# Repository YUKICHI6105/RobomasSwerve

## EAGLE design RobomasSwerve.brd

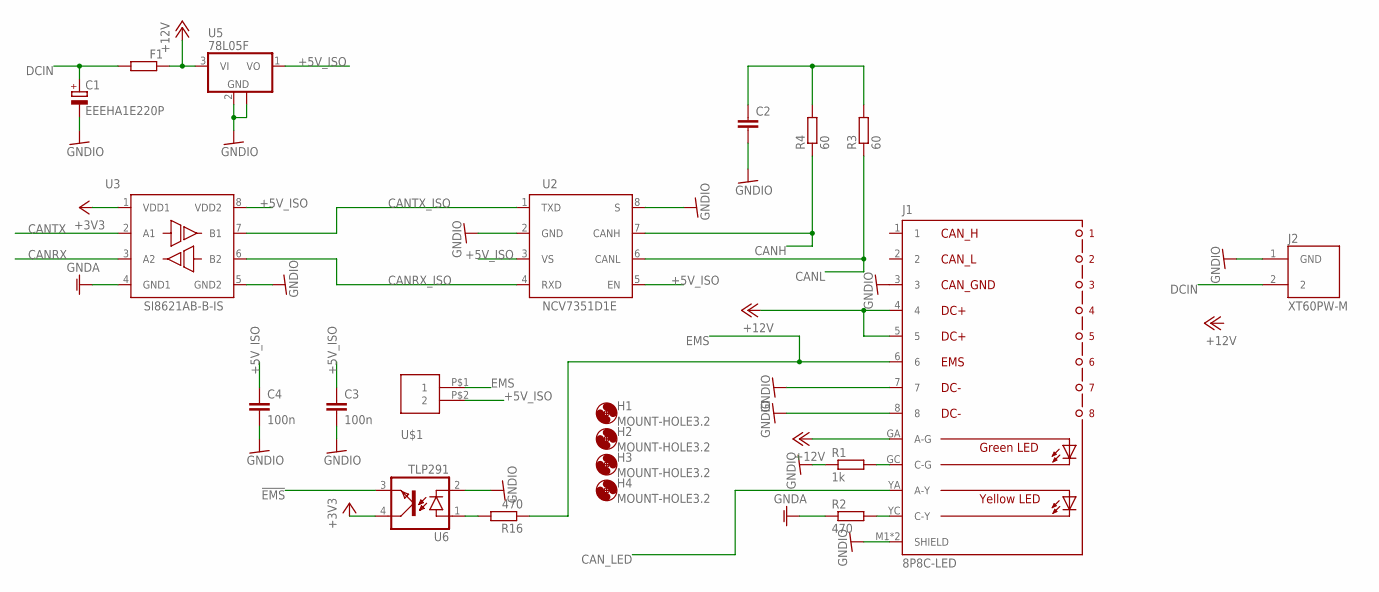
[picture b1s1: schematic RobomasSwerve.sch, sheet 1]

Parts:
C1: EEEHA1E220P; 153CLV-0605
C2: C-EUC0603; C0603
C3, C4: 100n; C0603
F1: R-EU_R1206; R1206
H1, H2, H3, H4: MOUNT-HOLE3.2; 3,2
J1: 8P8C-LED
J2: XT60PW-M; AMASS_XT60PW-M
R1: 1k; R0603
R2, R16: 470; R0603
R3, R4: 60; R0603
U2: NCV7351D1E; SO08
U3: SI8621AB-B-IS; SO08
U5: 78L05F; SOT89
U6: TLP291; MINI-FLAT-4
U$1: XH-2-STRAIGHT; CON-XH-2-STRAIGHT

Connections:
!EMS: U6.3 (EMIT); also elsewhere on the board
+3V3: U3.1 (VDD1), U6.4 (COL); also elsewhere on the board
+5V_ISO: C3.1, C4.1, U2.3 (VS), U2.5 (EN), U3.8 (VDD2), U5.1 (VO), U$1.P$2 (2)
+12V: F1.1, J1.4, J1.5, J1.GA (A-G), U5.3 (VI)
CANH: R4.1, U2.7 (CANH)
CANL: R3.1, U2.6 (CANL)
CANRX: U3.3 (A2); also elsewhere on the board
CANRX_ISO: U2.4 (RXD), U3.6 (B2)
CANTX: U3.2 (A1); also elsewhere on the board
CANTX_ISO: U2.1 (TXD), U3.7 (B1)
CAN_LED: J1.YA (A-Y); also elsewhere on the board
DCIN: C1.+, F1.2, J2.2
EMS: J1.6, R16.1, U$1.P$1 (1)
GNDA: R2.1, U3.4 (GND1); also elsewhere on the board
GNDIO: C1.-, C2.2, C3.2, C4.2, J1.3, J1.7, J1.8, J1.M1 (SHIELD), J1.M2 (SHIELD), J2.1 (GND), R1.1, U2.2 (GND), U2.8 (S), U3.5 (GND2), U5.2 (GND), U5.2@1 (GND), U6.2 (C)
unnamed: J1.GC (C-G), R1.2
unnamed: J1.YC (C-Y), R2.2
unnamed: C2.1, R3.2, R4.2
unnamed: R16.2, U6.1 (A)

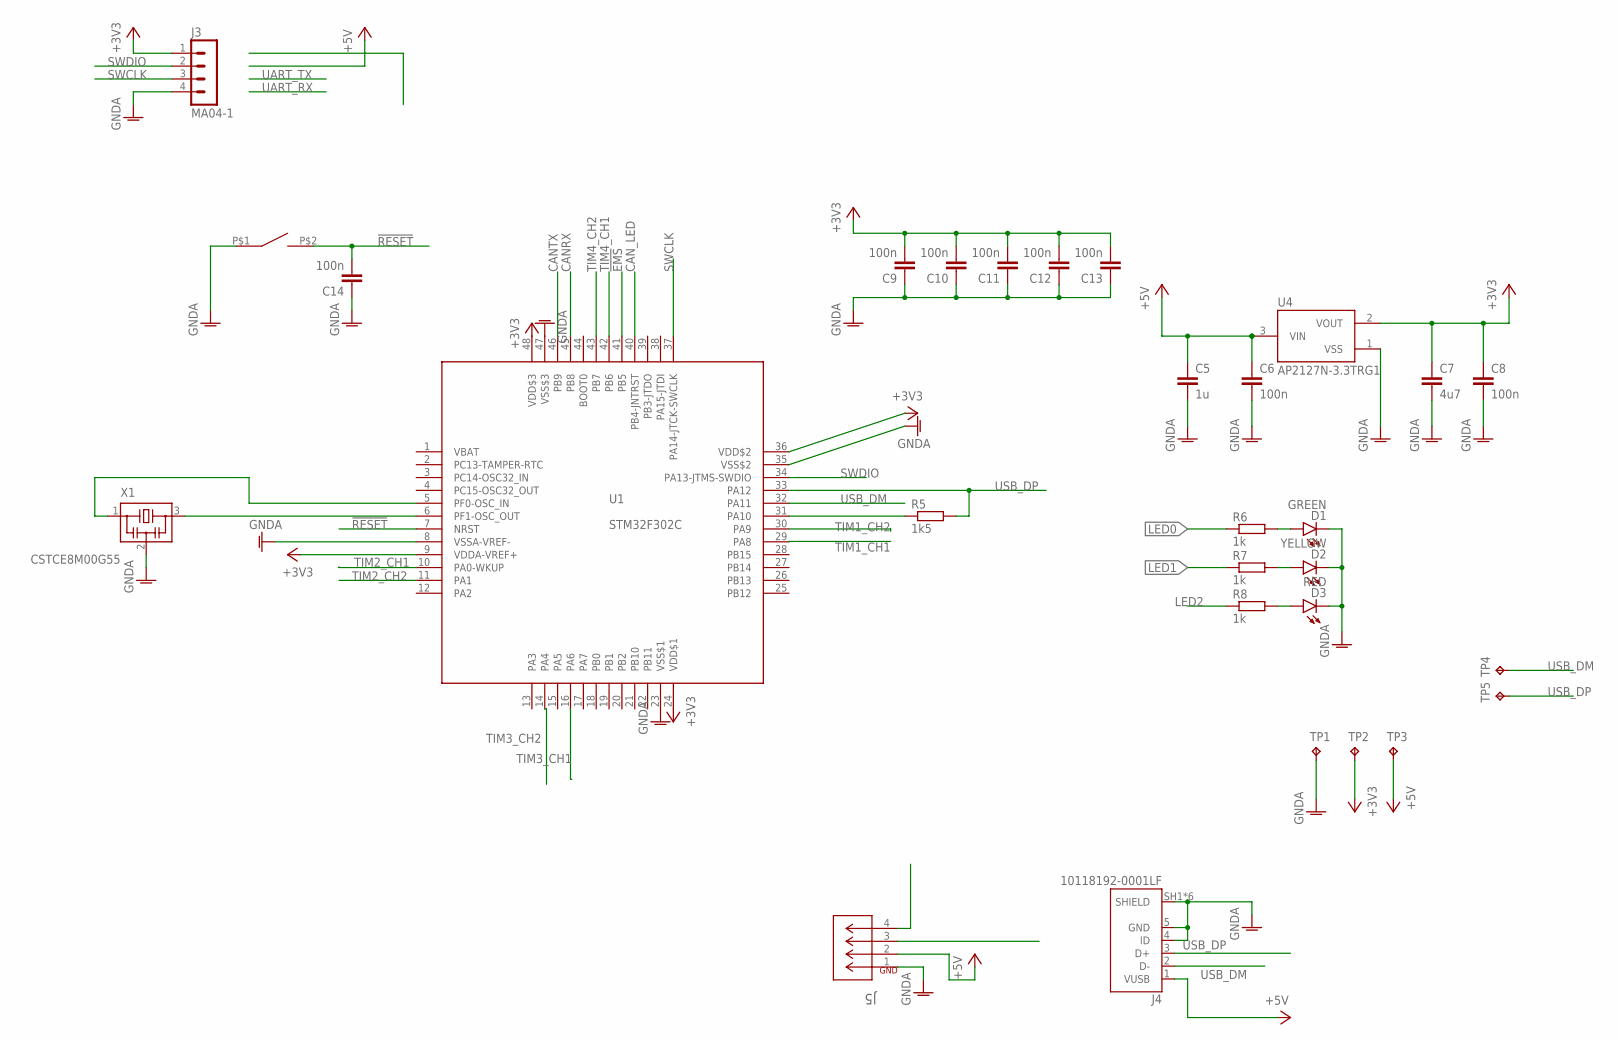
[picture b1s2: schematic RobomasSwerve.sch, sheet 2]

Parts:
C5: 1u; C0603
C6, C8, C9, C10, C11, C12, C13, C14: 100n; C0603
C7: 4u7; C0805
D1: GREEN; CHIPLED_0805
D2: YELLOW; CHIPLED_0805
D3: RED; CHIPLED_0805
J3: MA04-1
J4: 10118192-0001LF; AMPHENOL_10118192-0001LF
J5: EP2.5-4-SIDE; CONN4_1744426-4
R5: 1k5; R0603
R6, R7, R8: 1k; R0603
S1: SWITCH_TACTILETOP; SWITCH_TACTILE_3X6
TP1, TP2, TP3, TP4, TP5: TPB1,27; B1,27
U1: STM32F302C; LQFP48
U4: AP2127N-3.3TRG1; SOT95P240X110-3
X1: CSTCE8M00G55

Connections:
!EMS: U1.41 (PB5); also elsewhere on the board
!RESET: C14.2, S1.P$2 (2), U1.7 (NRST)
+3V3: C7.1, C8.1, C9.2, C10.2, C11.2, C12.2, C13.2, J3.1, TP2.TP, U1.9 (VDDA-VREF+), U1.24 (VDD$1), U1.36 (VDD$2), U1.48 (VDD$3), U4.2 (VOUT); also elsewhere on the board
+5V: C5.1, C6.1, J4.1 (VUSB), J5.2, TP3.TP, U4.3 (VIN)
CANRX: U1.45 (PB8); also elsewhere on the board
CANTX: U1.46 (PB9); also elsewhere on the board
CAN_LED: U1.40 (PB4-JNTRST); also elsewhere on the board
ENC_A: J5.3
ENC_B: J5.4
GNDA: C5.2, C6.2, C7.2, C8.2, C9.1, C10.1, C11.1, C12.1, C13.1, C14.1, D1.C, D2.C, D3.C, J3.4, J4.4 (ID), J4.5 (GND), J4.SH1 (SHIELD), J4.SH2 (SHIELD), J4.SH3 (SHIELD), J4.SH4 (SHIELD), J4.SH5 (SHIELD), J4.SH6 (SHIELD), J5.1, S1.P$1 (1), TP1.TP, U1.8 (VSSA-VREF-), U1.23 (VSS$1), U1.35 (VSS$2), U1.47 (VSS$3), U4.1 (VSS), X1.2; also elsewhere on the board
LED0: R6.1
LED1: R7.1
LED2: R8.1
unnamed: D2.A, R7.2
unnamed: D1.A, R6.2
unnamed: U1.6 (PF1-OSC_OUT), X1.3
unnamed: U1.5 (PF0-OSC_IN), X1.1
unnamed: R5.1, U1.31 (PA10)
unnamed: D3.A, R8.2
SWCLK: J3.3, U1.37 (PA14-JTCK-SWCLK)
SWDIO: J3.2, U1.34 (PA13-JTMS-SWDIO)
TIM1_CH1: U1.29 (PA8)
TIM1_CH2: U1.30 (PA9)
TIM2_CH1: U1.10 (PA0-WKUP)
TIM2_CH2: U1.11 (PA1)
TIM3_CH1: U1.16 (PA6)
TIM3_CH2: U1.14 (PA4)
TIM4_CH1: U1.42 (PB6)
TIM4_CH2: U1.43 (PB7)
USB_DM: J4.2 (D-), TP4.TP, U1.32 (PA11)
USB_DP: J4.3 (D+), R5.2, TP5.TP, U1.33 (PA12)

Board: 2 copper layers, 50 parts (1 on the bottom side), 31 nets, no tracks yet.
